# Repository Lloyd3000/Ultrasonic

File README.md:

# Ultrasonic Music Control

A small, driverless device that allows you to control your music with the wave of a hand.

This is a small device that youses the off the shelf Ultra sonic module "HC-SR04" and an Attiny 2313 to create, with the help of the VUSB library a Gesture Control interface for the Music control functions on your PC
!

Full text on "https://hackaday.io/project/2632-ultrasonic-music-control"

My Website "http://www.lloyd3000.com"

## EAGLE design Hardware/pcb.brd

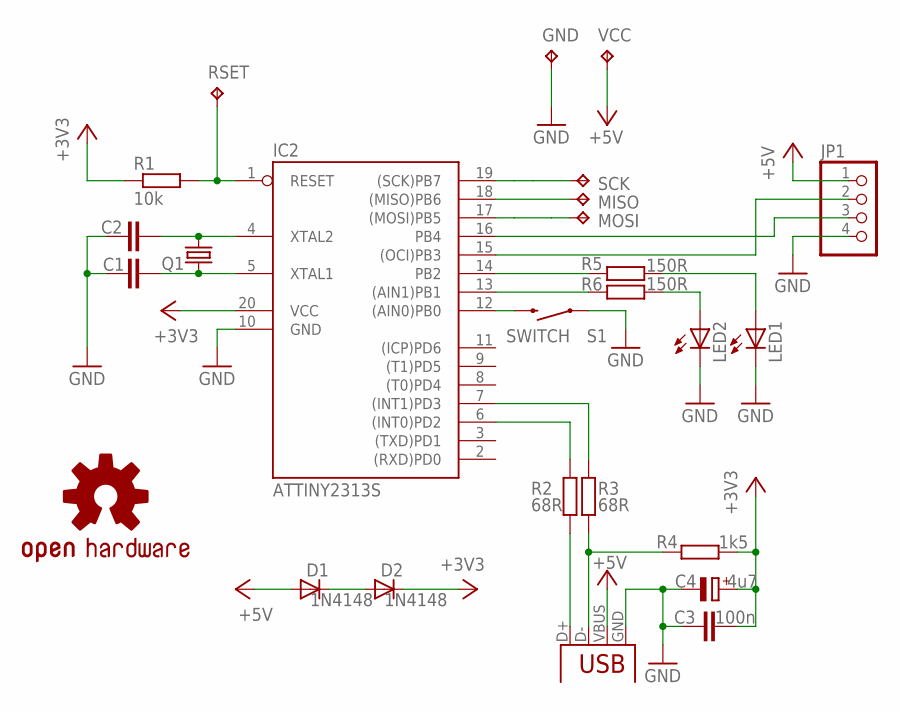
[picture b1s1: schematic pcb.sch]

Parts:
C1, C2: C-EUC1206; C1206
C3: 100n; C1206
C4: 4u7; PANASONIC_B
D1, D2: 1N4148; SMA-DIODE
GND: TPB2,54; B2,54
IC2: ATTINY2313S; SO20L
JP1: PINHD-1X4_2.54; 1X04
LED1, LED2: LED1206; LED-1206
LOGO1: OSHW-LOGOM; OSHW-LOGO-M
MISO: TPB2,54; B2,54
MOSI: TPB2,54; B2,54
Q1: CRYSTALSMD; HC49UP
R1: 10k; R1206
R2, R3: 68R; R1206
R4: 1k5; R1206
R5, R6: 150R; R1206
RSET: TPB2,54; B2,54
S1: SWITCH; TACTILE-SWITCH-1101NE
SCK: TPB2,54; B2,54
VCC: TPB2,54; B2,54
X1: USB-MICROB

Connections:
+3V3: C3.2, C4.+, D2.C, IC2.20 (VCC), R1.1, R4.1
+5V: D1.A, JP1.1, VCC.TP, X1.VBUS
GND: C1.1, C2.1, C3.1, C4.-, GND.TP, IC2.10 (GND), JP1.4, LED1.C, LED2.C, S1.P$1 (1), X1.GND
unnamed: C1.2, IC2.5 (XTAL1), Q1.1
unnamed: C2.2, IC2.4 (XTAL2), Q1.2
unnamed: IC2.1 (RESET), R1.2, RSET.TP
unnamed: LED2.A, R6.2
unnamed: IC2.14 (PB2), R5.1
unnamed: IC2.13 ((AIN1)PB1), R6.1
unnamed: LED1.A, R5.2
unnamed: R2.1, X1.D+
unnamed: R3.1, R4.2, X1.D-
unnamed: IC2.12 ((AIN0)PB0), S1.P$2 (2)
unnamed: IC2.15 ((OCI)PB3), JP1.2
unnamed: IC2.16 (PB4), JP1.3
unnamed: IC2.6 ((INT0)PD2), R2.2
unnamed: IC2.7 ((INT1)PD3), R3.2
unnamed: D1.C, D2.A
unnamed: IC2.19 ((SCK)PB7), SCK.TP
unnamed: IC2.18 ((MISO)PB6), MISO.TP
unnamed: IC2.17 ((MOSI)PB5), MOSI.TP

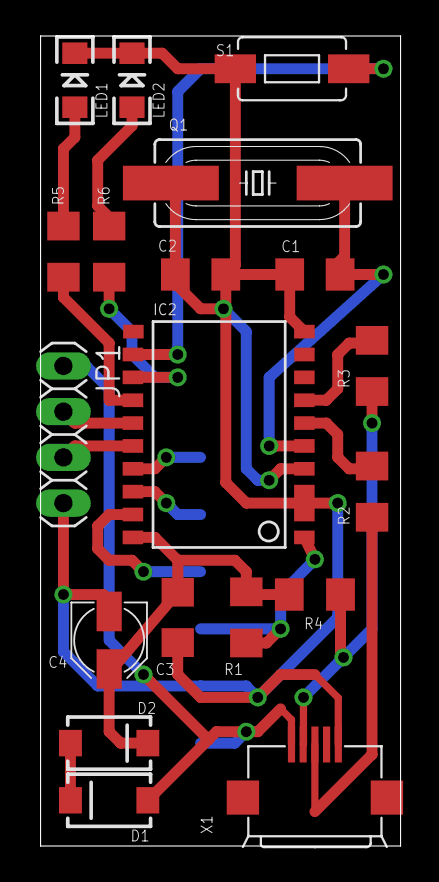
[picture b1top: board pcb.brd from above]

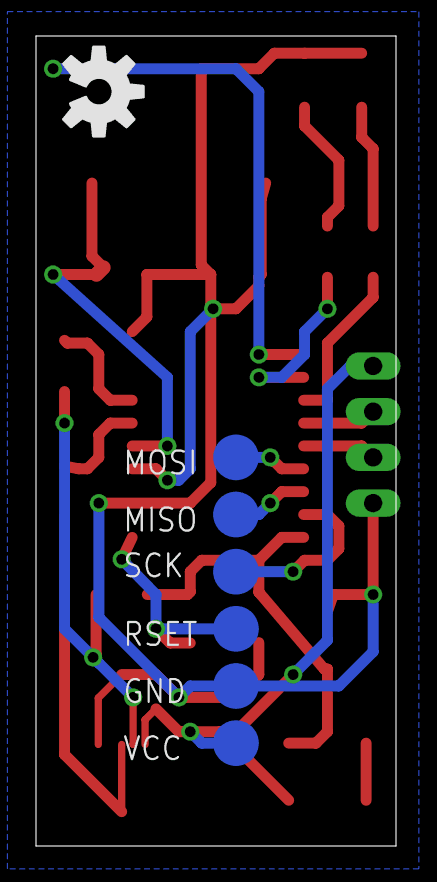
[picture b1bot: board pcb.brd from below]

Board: 2 copper layers, 20.0 x 45.0 mm, 26 parts (7 on the bottom side), 21 nets.

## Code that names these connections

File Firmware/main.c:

/*************************************************************************
Title:    Ultrasonic Volume Control
Author:   Elias Fröhlich 
Web: http://hackaday.io/project/2632-Ultrasonic-Volume-Control
**************************************************************************/

#define f_cpu 16000000
#include <avr/io.h>
#include <avr/interrupt.h>
#include <avr/wdt.h>
#include <util/delay.h>

#include "usbdrv.h"

//The USB Hid Report Handler that tells the PC what data to expect
PROGMEM char usbHidReportDescriptor[USB_CFG_HID_REPORT_DESCRIPTOR_LENGTH] = {
    0x05, 0x0c,                    // USAGE_PAGE (Consumer Devices)
    0x09, 0x01,                    // USAGE (Consumer Control)
    0xa1, 0x01,                    // COLLECTION (Application)
    0x85, 0x01,                    //   REPORT_ID (1)
    0x19, 0x00,                    //   USAGE_MINIMUM (Unassigned)
    0x2a, 0x3c, 0x02,              //   USAGE_MAXIMUM (AC Format)
    0x15, 0x00,                    //   LOGICAL_MINIMUM (0)
    0x26, 0x3c, 0x02,              //   LOGICAL_MAXIMUM (572)
    0x95, 0x01,                    //   REPORT_COUNT (1)
    0x75, 0x10,                    //   REPORT_SIZE (16)
    0x81, 0x00,                    //   INPUT (Data,Var,Abs)
    0xc0                           // END_COLLECTION  
};

//Declare some variables
typedef struct {
	uint8_t modifier;
	uint8_t reserved;
	uint8_t keycode[2];
} keyboard_report_t;

static uchar reportBuffer[3] = {0,0,0} ;
volatile int test;
volatile uchar KeyPressed = 0;
static keyboard_report_t keyboard_report; 

static uchar idleRate; 


//set up the USB connection
usbMsgLen_t usbFunctionSetup(uchar data[8]) {
    usbRequest_t *rq = (void *)data;

    if((rq->bmRequestType & USBRQ_TYPE_MASK) == USBRQ_TYPE_CLASS) {
        switch(rq->bRequest) {
        case USBRQ_HID_GET_REPORT: // send "no keys pressed" if asked here
            // wValue: ReportType (highbyte), ReportID (lowbyte)
            usbMsgPtr = (void *)&keyboard_report; // we only have this one
            keyboard_report.modifier = 0;
            keyboard_report.keycode[0] = 0;
            return sizeof(keyboard_report);
		case USBRQ_HID_SET_REPORT: // if wLength == 1, should be LED state
            return (rq->wLength.word == 1) ? USB_NO_MSG : 0;
        case USBRQ_HID_GET_IDLE: // send idle rate to PC as required by spec
            usbMsgPtr = &idleRate;
            return 1;
        case USBRQ_HID_SET_IDLE: // save idle rate as required by spec
            idleRate = rq->wValue.bytes[1];
            return 0;
        }
    }
    
    return 0; // by default don't return any data
}


int main() {

	unsigned int count;
	
	int i;
	
	unsigned char  set = 0, send = 0, on = 1, times = 1;
	
	DDRB = 0b00001110; // PB1,2,3 as output rest is input
	PORTB |= 1 << PB0; // PB0 is input with internal pullup resistor activated
	PORTB |= 1 << PB4; // PB4 is input with internal pullup resistor activated    
    wdt_enable(WDTO_1S); // enable 1s watchdog timer

	PORTB |= (1 << PB2); //LED1 on
	PORTB &= ~(1 << PB1);  //LED2 off
			
    usbInit();
	
    usbDeviceDisconnect(); // enforce re-enumeration
    for(i = 0; i<250; i++) { // wait 500 ms
        wdt_reset(); // keep the watchdog happy
        _delay_ms(2);
    }
	
    usbDeviceConnect();
	
	reportBuffer[0] = 1;  // ReportID = 1
	reportBuffer[2] = 0;  
	
  
    sei(); // Enable interrupts after re-enumeration
	
    while(1) {
        wdt_reset(); // keep the watchdog happy
        usbPoll();

			
		if(!(PINB & (1<<PB0))) { // button pressed (PB1 at ground voltage)
			
			 if(on == 1){
			on = 0;
			PORTB &= ~(1 << PB2); // Triggerline turn on	
			PORTB |= (1 << PB1); 
			}
			else{
			PORTB |= (1 << PB2); 
			PORTB &= ~(1 << PB1); // Triggerline turn on	
			on = 1;
			}
		
			for(i = 0; i<250; i++) { // wait 500 ms
			usbPoll();
			wdt_reset(); // keep the watchdog happy
			_delay_ms(2);
			} 
			
		}


		if(on == 1){
		
		
		//Sending th trig signal
		PORTB |= (1 << PB3); 
		_delay_us(10);
		PORTB &= ~(1 << PB3);


		//Polling the Input pin
		for(i = 0; i<1250; i++) { 
		
			wdt_reset(); // keep the watchdog happy
			usbPoll();
	
			if((PINB & (1<<PB4))){
			count ++;

			}else{

			}
			_delay_us(5);
		}	



		//what key is pressed?
		
		if((count <= 80)&(set == 0)){
		
			KeyPressed = 0xCD;
			send = 1;
			times = 1;
			set = 1;
			
		}else if((count >= 81) & (count <= 140)){

			KeyPressed = 0xEA;
			send = 1;
			times = 10;
			
		}else if((count >= 140) & (count <= 258)){

			KeyPressed = 0xE9;
			send = 1;
			times = 10;
			
		}else{

			set = 0;
		
		} 
		
		
	//Send the KEy
		if((send == 1)){
		

			
		while(times>=1){
				usbPoll();
				wdt_reset(); // keep the watchdog happy		
			times --;
			
			reportBuffer[1] = KeyPressed;
			usbSetInterrupt(reportBuffer, sizeof(reportBuffer));
			
			_delay_ms(10); //	
							 			
			reportBuffer[1] = 0x00;
			usbSetInterrupt(reportBuffer, sizeof(reportBuffer));
			
			_delay_ms(10); //		 
		}

		PORTB |= (1 << PB1); //LED on
		PORTB |= (1 << PB2); //LED on

			for(i = 0; i<150; i++) { // wait 300 ms
				usbPoll();
				wdt_reset(); // keep the watchdog happy
				_delay_ms(2);
			}
			
			PORTB &= ~(1 << PB1); // Triggerline turn on	
			PORTB |= (1 << PB2); 		
			
		send = 0;
		
		}
		
		}
		
		
		count = 0;
		

		
		
    }
	
    return 0;
}

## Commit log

2015-04-04 :confetti_ball: Added .gitattributes & .gitignore files
2015-04-04 Revert ":confetti_ball: Added .gitattributes & .gitignore files"
    This reverts commit b7f8ce8fbccd0dedbcca2f15cc4f9f2b6b560fe9.
2015-04-04 test
    test

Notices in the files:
parts and their libraries:
SparkFun-Aesthetics: Licensing: CC v3.0 Share-Alike You are welcome to use this library for commercial purposes.
